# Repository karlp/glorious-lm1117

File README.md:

## Heating things with Quiescent current

See https://github.com/karlp/zypsnips/blob/master/lm1117.replacements.for.glory.md

Demo PCB to show off how horrificall inefficient LM1117 style devices are.

5mA Iq! Do _not_ use these parts! It's the 21st century! you can do better!

## Particulars

LM1117 family parts specify "typical" Iq of 5mA.  Power losses are P=VI, with V being the Vin
So 40x5x5e-3 = ~1W of wasted power.  It's _probably_ not actually possible to pack this tight
to actually get any meaningful heat raise, but the idea is to at least demonstrate that with
a ~zero load, you still consume serious power.

Things we've shortcutted with:
* LM1117 specifes ~2mA minimum load required to ensure regulation.  hah, like we care
  about regulation anywya
* LM1117 _prefers_ to have input capacitance, but admits that the power supply caps may
  be sufficient.
* LM1117 specifies min 10uF output capacitance.  We're going to yolo that, for demo purposes.

## Thanks
Mad props to the l33t hacking crew in HASHHASHGD32, as always.

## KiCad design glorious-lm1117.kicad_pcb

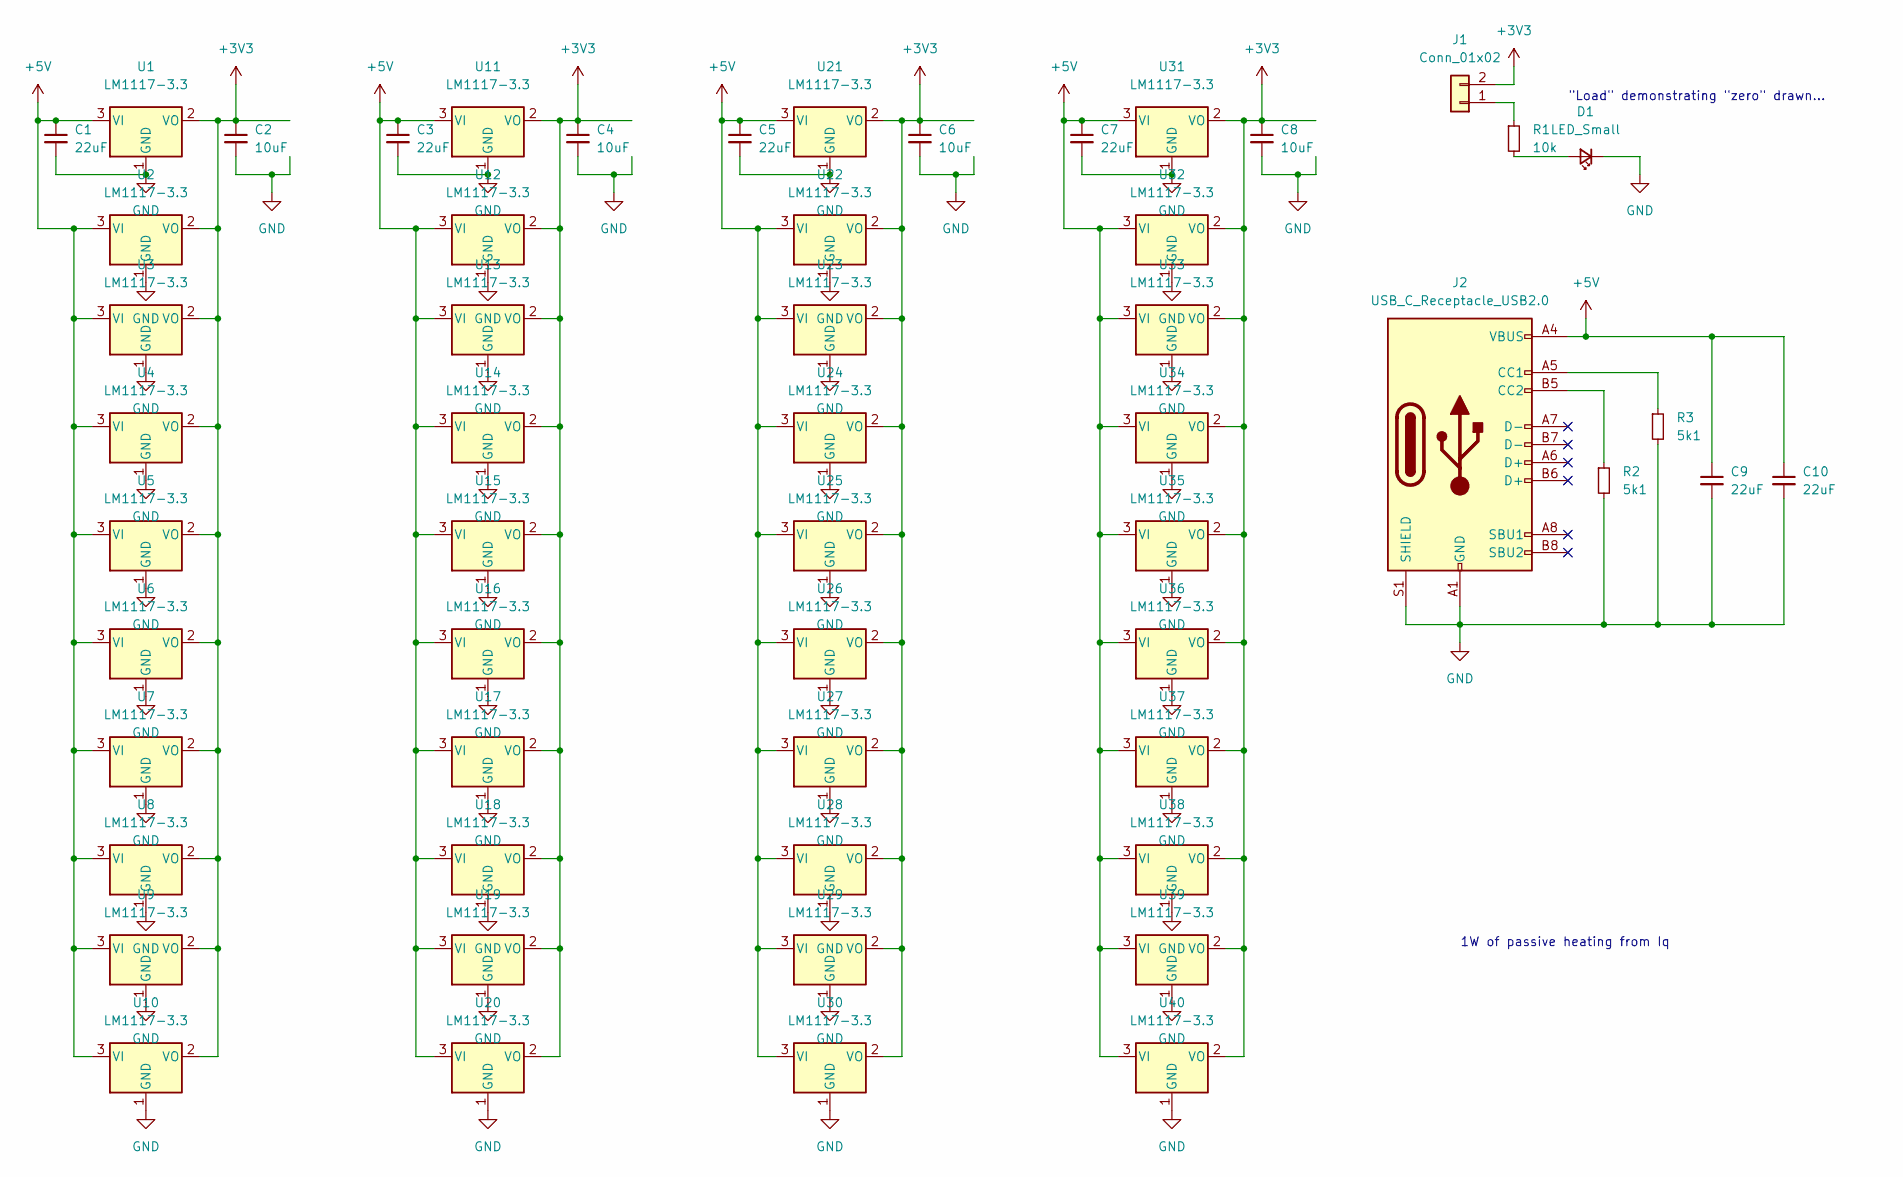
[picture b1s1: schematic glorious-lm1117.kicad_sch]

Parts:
C1, C3, C5, C7, C9, C10: 22uF; C_0805_2012Metric
C2, C4, C6, C8: 10uF; C_0805_2012Metric
D1: LED_Small; LED_0603_1608Metric
J1: Conn_01x02; PinHeader_1x02_P2.54mm_Vertical
J2: USB_C_Receptacle_USB2.0; USB_C_Receptacle_XKB_U262-16XN-4BVC11
R1: 10k; R_0603_1608Metric
R2, R3: 5k1; R_0603_1608Metric
U1, U2, U3, U4, U5, U6, U7, U8, U9, U10, U11, U12, U13, U14, U15, U16, U17, U18, U19, U20, U21, U22, U23, U24, U25, U26, U27, U28, U29, U30, U31, U32, U33, U34, U35, U36, U37, U38, U39, U40: LM1117-3.3; SOT-223-3_TabPin2

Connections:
+3V3: C2.1, C4.1, C6.1, C8.1, J1.2, U1.2 (VO), U2.2 (VO), U3.2 (VO), U4.2 (VO), U5.2 (VO), U6.2 (VO), U7.2 (VO), U8.2 (VO), U9.2 (VO), U10.2 (VO), U11.2 (VO), U12.2 (VO), U13.2 (VO), U14.2 (VO), U15.2 (VO), U16.2 (VO), U17.2 (VO), U18.2 (VO), U19.2 (VO), U20.2 (VO), U21.2 (VO), U22.2 (VO), U23.2 (VO), U24.2 (VO), U25.2 (VO), U26.2 (VO), U27.2 (VO), U28.2 (VO), U29.2 (VO), U30.2 (VO), U31.2 (VO), U32.2 (VO), U33.2 (VO), U34.2 (VO), U35.2 (VO), U36.2 (VO), U37.2 (VO), U38.2 (VO), U39.2 (VO), U40.2 (VO)
+5V: C1.1, C3.1, C5.1, C7.1, C9.1, C10.1, J2.A4 (VBUS), J2.A9 (VBUS), J2.B4 (VBUS), J2.B9 (VBUS), U1.3 (VI), U2.3 (VI), U3.3 (VI), U4.3 (VI), U5.3 (VI), U6.3 (VI), U7.3 (VI), U8.3 (VI), U9.3 (VI), U10.3 (VI), U11.3 (VI), U12.3 (VI), U13.3 (VI), U14.3 (VI), U15.3 (VI), U16.3 (VI), U17.3 (VI), U18.3 (VI), U19.3 (VI), U20.3 (VI), U21.3 (VI), U22.3 (VI), U23.3 (VI), U24.3 (VI), U25.3 (VI), U26.3 (VI), U27.3 (VI), U28.3 (VI), U29.3 (VI), U30.3 (VI), U31.3 (VI), U32.3 (VI), U33.3 (VI), U34.3 (VI), U35.3 (VI), U36.3 (VI), U37.3 (VI), U38.3 (VI), U39.3 (VI), U40.3 (VI)
GND: C1.2, C2.2, C3.2, C4.2, C5.2, C6.2, C7.2, C8.2, C9.2, C10.2, D1.1 (K), J2.A1 (GND), J2.A12 (GND), J2.B1 (GND), J2.B12 (GND), J2.S1 (SHIELD), R2.2, R3.2, U1.1 (GND), U2.1 (GND), U3.1 (GND), U4.1 (GND), U5.1 (GND), U6.1 (GND), U7.1 (GND), U8.1 (GND), U9.1 (GND), U10.1 (GND), U11.1 (GND), U12.1 (GND), U13.1 (GND), U14.1 (GND), U15.1 (GND), U16.1 (GND), U17.1 (GND), U18.1 (GND), U19.1 (GND), U20.1 (GND), U21.1 (GND), U22.1 (GND), U23.1 (GND), U24.1 (GND), U25.1 (GND), U26.1 (GND), U27.1 (GND), U28.1 (GND), U29.1 (GND), U30.1 (GND), U31.1 (GND), U32.1 (GND), U33.1 (GND), U34.1 (GND), U35.1 (GND), U36.1 (GND), U37.1 (GND), U38.1 (GND), U39.1 (GND), U40.1 (GND)
unnamed: J1.1, R1.1
unnamed: J2.A5 (CC1), R3.1
unnamed: J2.B5 (CC2), R2.1
unnamed: D1.2 (A), R1.2

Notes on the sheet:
1W of passive heating from Iq
"Load" demonstrating "zero" drawn...

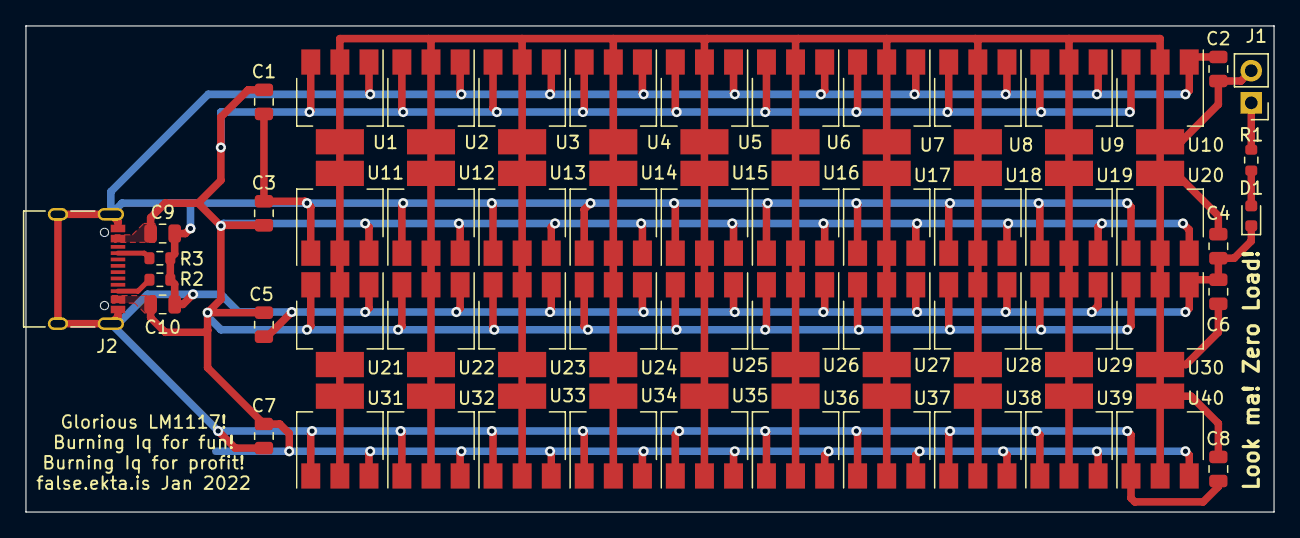
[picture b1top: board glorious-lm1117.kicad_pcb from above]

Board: 2 copper layers, 98.6 x 38.4 mm, 56 parts (0 on the bottom side), 7 nets.

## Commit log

2022-01-10 glory
2022-01-10 so read things maybe
2022-01-10 finished? needs more obnoxious silk perhaps?
2022-01-10 A little more on how
2022-01-10 example pdf schematic
2022-01-10 demo pcb view for right now
2024-08-02 add ibom file
